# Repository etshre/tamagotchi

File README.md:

<h1>TAMAGOTCHI!!! MY FIRST HARDWARE PROJECT YAYAY!</h1>

<h3>short description of my project</h3>
<p>My project is to make a tamagotchi following the Fallout tutorial. Fallout is a YSWS by Hack Club, hosting a 7 day hackathon in Shenzen. There is an OLED screen, with 3 buttons controlling what the Tamagotchi does and a buzzer to output sounds.</p>

<h3>why i made the project </h3> 
<p>This is my first hardware project, and I really hope that I will be able to make lots of cool hardware, learn new skills and qualify for the hackathon in Shenzen.</p>

<h3>how to use my project</h3> 
<p>N/A rn</p>

<h3>Pictures of my project:</h3>

<h3>A screenshot of a full 3D model of your project</h3>
<p>N/A for now</p>

<h3>A screenshot of your PCB, if you have one</h3>

<h3>BOM (Bill of Materials) in table format at the end of the README, with links.</h3>

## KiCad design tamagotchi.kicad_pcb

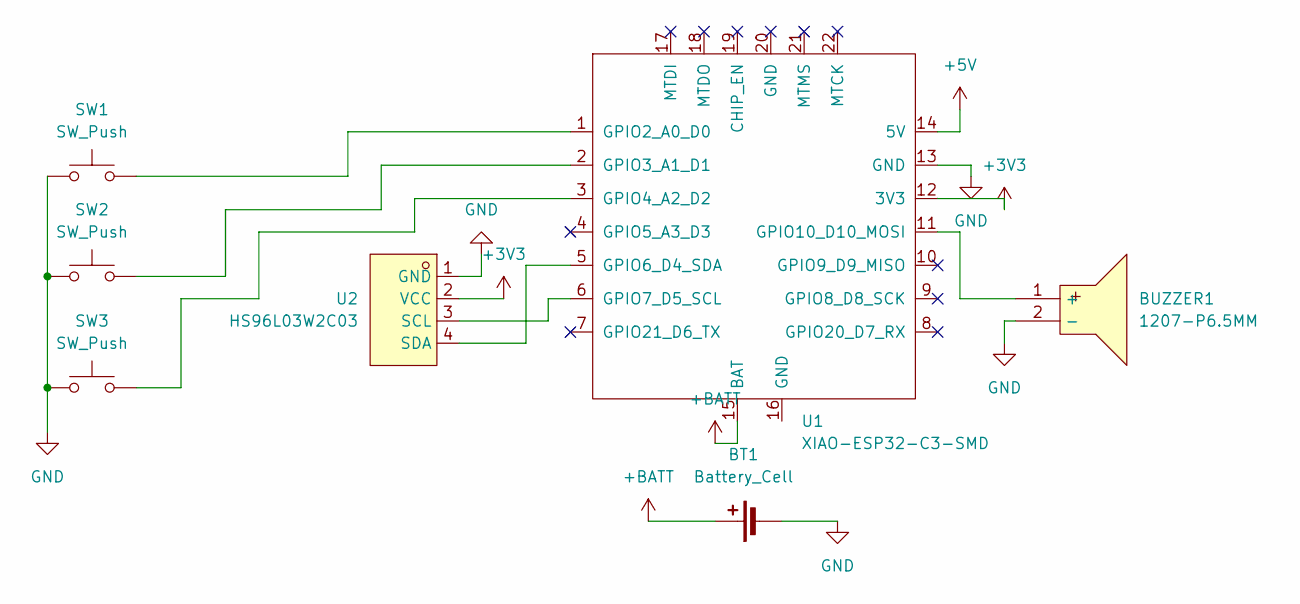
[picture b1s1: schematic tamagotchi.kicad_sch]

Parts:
BT1: Battery_Cell; PinHeader_1x02_P2.54mm_Vertical
BUZZER1: 1207-P6.5MM; BUZ-TH_BD12.5-P6.50-D1.4; MPN 1207-P6.5MM; LCSC Part C49246964
SW1, SW2, SW3: SW_Push; SW-TH_4P-L4.5-W4.5-P3.00-LS4.8
U1: XIAO-ESP32-C3-SMD; XIAO-ESP32-C3-DIP-SMD
U2: HS96L03W2C03; OLED-TH_L27.8-W27.2-P2.54_C9900033791; MPN HS96L03W2C03; LCSC Part C5248080

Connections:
+3V3: U1.12 (3V3), U2.2 (VCC)
+5V: U1.14 (5V)
+BATT: BT1.1 (+), U1.15 (BAT)
GND: BT1.2 (-), BUZZER1.2 (-), SW1.1, SW2.1, SW3.1, U1.13 (GND), U2.1 (GND)
unnamed: BUZZER1.1 (+), U1.11 (GPIO10_D10_MOSI)
unnamed: SW1.2, U1.1 (GPIO2_A0_D0)
unnamed: SW2.2, U1.2 (GPIO3_A1_D1)
unnamed: SW3.2, U1.3 (GPIO4_A2_D2)
unnamed: U1.5 (GPIO6_D4_SDA), U2.4 (SDA)
unnamed: U1.6 (GPIO7_D5_SCL), U2.3 (SCL)

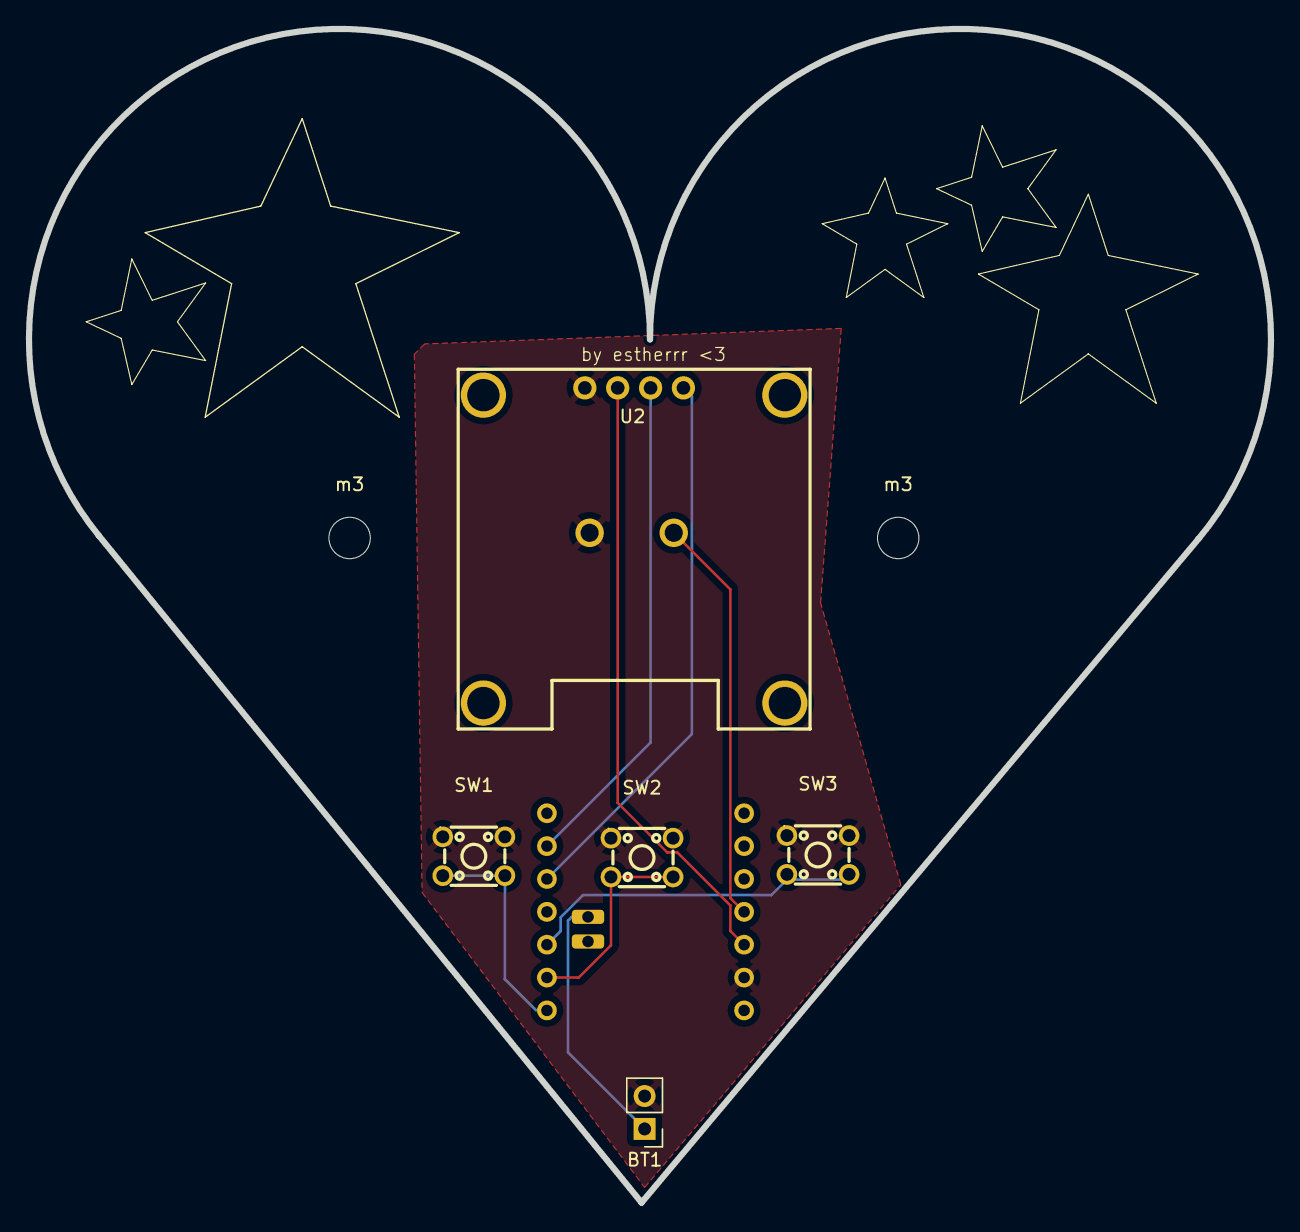
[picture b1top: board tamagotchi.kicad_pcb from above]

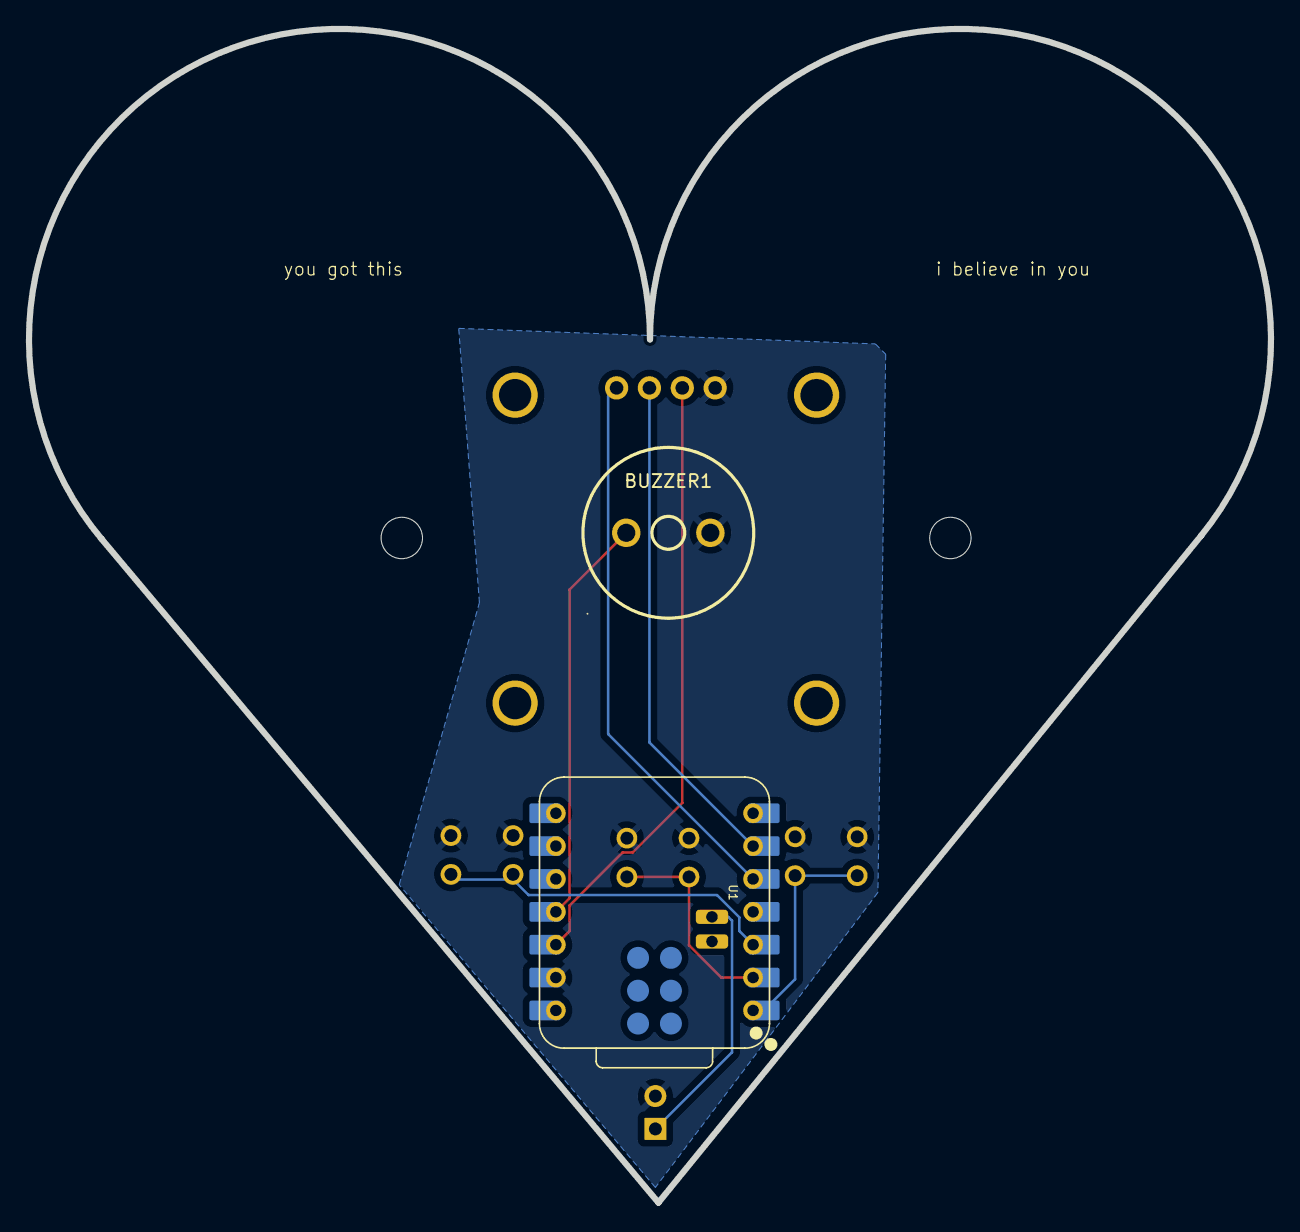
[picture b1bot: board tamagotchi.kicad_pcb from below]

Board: 2 copper layers, 96.0 x 90.7 mm, 9 parts (2 on the bottom side), 9 nets.

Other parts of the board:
m3, m3#2: MountingHole_3.2mm_M3

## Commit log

2026-05-23 make pcb
2026-05-23 add gerbers
2026-05-23 move 3d view
2026-05-23 Add initial README for Tamagotchi hardware project
2026-05-24 add new gerber files and changed the footprint mapping of the XIAO
2026-05-27 fixed button and xiao overlap
2026-05-29 exporting step file
